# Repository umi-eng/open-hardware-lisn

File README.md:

# Open Hardware Dual DC LISN

This is a line impedance stabilization network for measuring conducted emissions to aid in evaluating designs for EMC compliance. It's based on an existing design from Rhode & Schwarz, which only existed as Gerber outputs.

This design is intended as a development tool and not suitable for empirical compliance testing.

## References

- [A homemade LISN for precompliance conducted emission tests on DC-DC power supplies - Rhode & Schwarz](https://www.rohde-schwarz.com/au/applications/a-homemade-lisn-for-precompliance-conducted-emission-tests-on-dc-dc-power-supplies_56279-1010752.html)

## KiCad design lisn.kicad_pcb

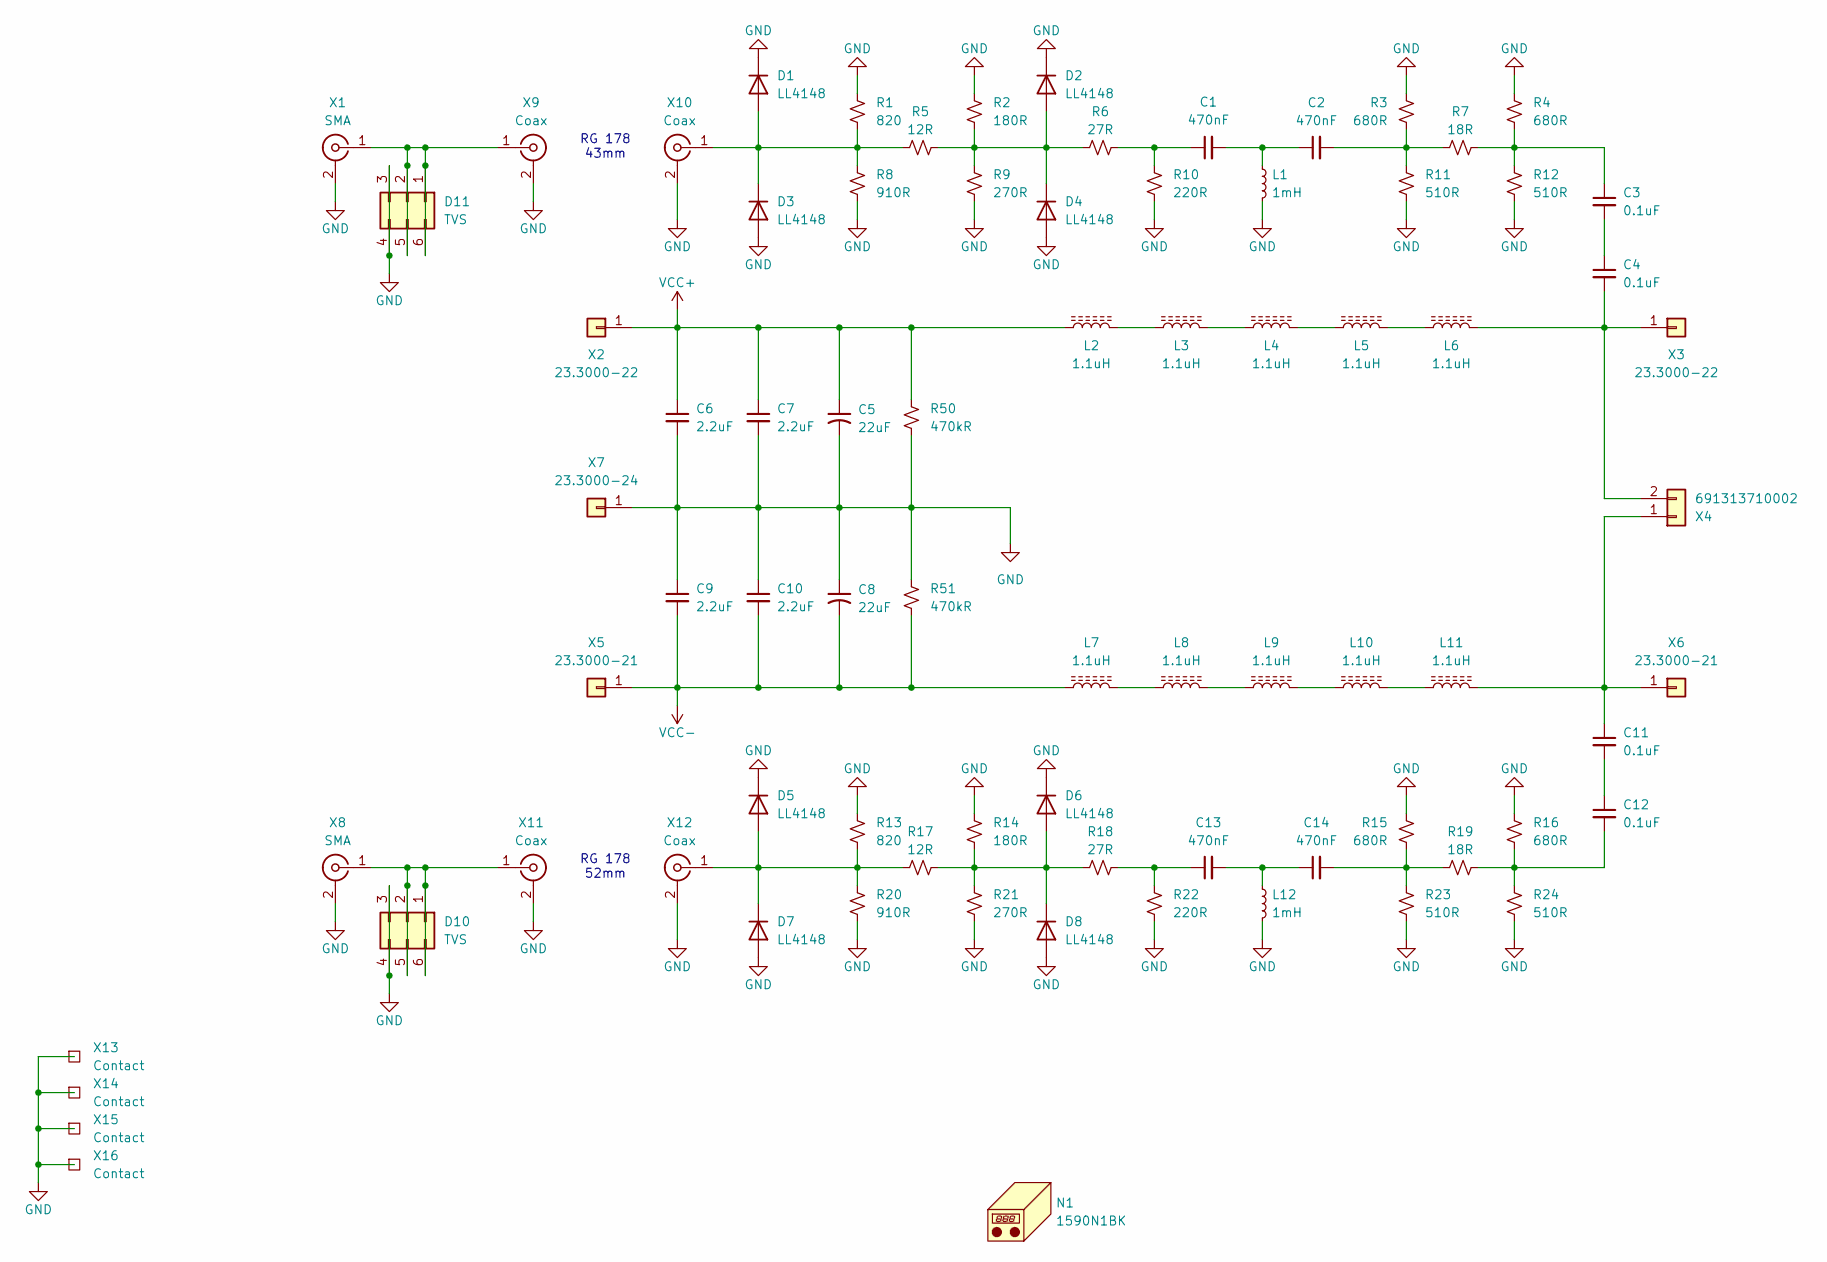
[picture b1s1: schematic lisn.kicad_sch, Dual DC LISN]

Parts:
C1, C2, C13, C14: 470nF; C_0805_2012Metric; Voltage 50V; Mouser 710-885012207102
C3, C4, C11, C12: 0.1uF; C_1206_3216Metric; Voltage 250V; Mouser 710-885342208004
C5, C8: 22uF; CP_Elec_8x10.5; Voltage 100V; Mouser 710-865060853003
C6, C7, C9, C10: 2.2uF; C_1210_3225Metric; Voltage 100V; Mouser 710-885012209071
D1, D2, D3, D4, D5, D6, D7, D8: LL4148; D_MiniMELF; Mouser 78-LL4148-M-08
D10, D11: TVS; DFN-6_1.3x1.2mm_P0.4mm; Mouser 710-824012823
L1, L12: 1mH; L_Wuerth_HCI-5040; Mouser 710-74404054102
L2, L3, L4, L5, L6, L7, L8, L9, L10, L11: 1.1uH; L_Wuerth_HCI-7050; Mouser 710-744314110
N1: 1590N1BK; Mouser 546-1590N1-BK
R1, R13: 820; R_0603_1608Metric; Mouser 667-ERJ-3EKF8200V
R2, R14: 180R; R_0603_1608Metric; Mouser 667-ERJ-3EKF1800V
R3, R4, R15, R16: 680R; R_0603_1608Metric; Mouser 667-ERJ-3EKF6800V
R5, R17: 12R; R_0603_1608Metric; Mouser 667-ERJ-3EKF12R0V
R6, R18: 27R; R_0603_1608Metric; Mouser 667-ERJ-3EKF27R0V
R7, R19: 18R; R_0603_1608Metric; Mouser 667-ERJ-3EKF18R0V
R8, R20: 910R; R_0603_1608Metric; Mouser 667-ERJ-3EKF9100V
R9, R21: 270R; R_0603_1608Metric; Mouser 667-ERJ-3EKF2700V
R10, R22: 220R; R_0603_1608Metric; Mouser 667-ERJ-3EKF2200V
R11, R12, R23, R24: 510R; R_0603_1608Metric; Mouser 667-ERJ-3EKF5100V
R50, R51: 470kR; R_0603_1608Metric; Mouser 667-ERJ-3EKF4703V
X1, X8: SMA; SMA_Amphenol_132289_EdgeMount; Mouser 710-60312242114510
X2, X3: 23.3000-22; STAUBLI_23.3000-22_Red
X4: 691313710002; PhoenixContact_MSTBA_2,5_2-G-5,08_1x02_P5.08mm_Horizontal; Mouser 710-691313710002
X5, X6: 23.3000-21; STAUBLI_23.3000-21_Black
X7: 23.3000-24; STAUBLI_23.3000-24_Yellow
X9, X10, X11, X12: Coax; Jumper_RG178
X13, X14, X15, X16: Contact; Wurth_331161702513; Mouser 710-331161702513

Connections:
GND: C5.2, C6.2, C7.2, C8.1, C9.1, C10.1, D1.1 (K), D2.1 (K), D3.2 (A), D4.2 (A), D5.1 (K), D6.1 (K), D7.2 (A), D8.2 (A), D10.3, D10.4, D11.3, D11.4, L1.2, L12.2, R1.1, R2.1, R3.1, R4.1, R8.2, R9.2, R10.2, R11.2, R12.2, R13.1, R14.1, R15.1, R16.1, R20.2, R21.2, R22.2, R23.2, R24.2, R50.2, R51.1, X1.2 (Ext), X7.1 (Pin_1_1), X8.2 (Ext), X9.2 (Ext), X10.2 (Ext), X11.2 (Ext), X12.2 (Ext), X13.1 (1_1), X14.1 (1_1), X15.1 (1_1), X16.1 (1_1)
unnamed: C1.1, R6.2, R10.1
unnamed: C1.2, C2.1, L1.1
unnamed: C2.2, R3.2, R7.1, R11.1
unnamed: C3.1, R4.2, R7.2, R12.1
unnamed: C3.2, C4.1
unnamed: C11.2, C12.1
unnamed: C12.2, R16.2, R19.2, R24.1
unnamed: C13.1, R18.2, R22.1
unnamed: C13.2, C14.1, L12.1
unnamed: C14.2, R15.2, R19.1, R23.1
unnamed: D1.2 (A), D3.1 (K), R1.2, R5.1, R8.1, X10.1 (In)
unnamed: D2.2 (A), D4.1 (K), R2.2, R5.2, R6.1, R9.1
unnamed: D5.2 (A), D7.1 (K), R13.2, R17.1, R20.1, X12.1 (In)
unnamed: D6.2 (A), D8.1 (K), R14.2, R17.2, R18.1, R21.1
unnamed: D10.1, D10.2, D10.5, D10.6, X8.1 (In), X11.1 (In)
unnamed: D11.1, D11.2, D11.5, D11.6, X1.1 (In), X9.1 (In)
unnamed: L2.2, L3.1
unnamed: L3.2, L4.1
unnamed: L4.2, L5.1
unnamed: L5.2, L6.1
unnamed: L7.2, L8.1
unnamed: L8.2, L9.1
unnamed: L9.2, L10.1
unnamed: L10.2, L11.1
unnamed: C4.2, L6.2, X3.1 (Pin_1_1), X4.2
unnamed: C11.1, L11.2, X4.1, X6.1 (Pin_1_1)
VCC+: C5.1, C6.1, C7.1, L2.1, R50.1, X2.1 (Pin_1_1)
VCC-: C8.2, C9.2, C10.2, L7.1, R51.2, X5.1 (Pin_1_1)

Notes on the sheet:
RG 178 52mm
RG 178 43mm

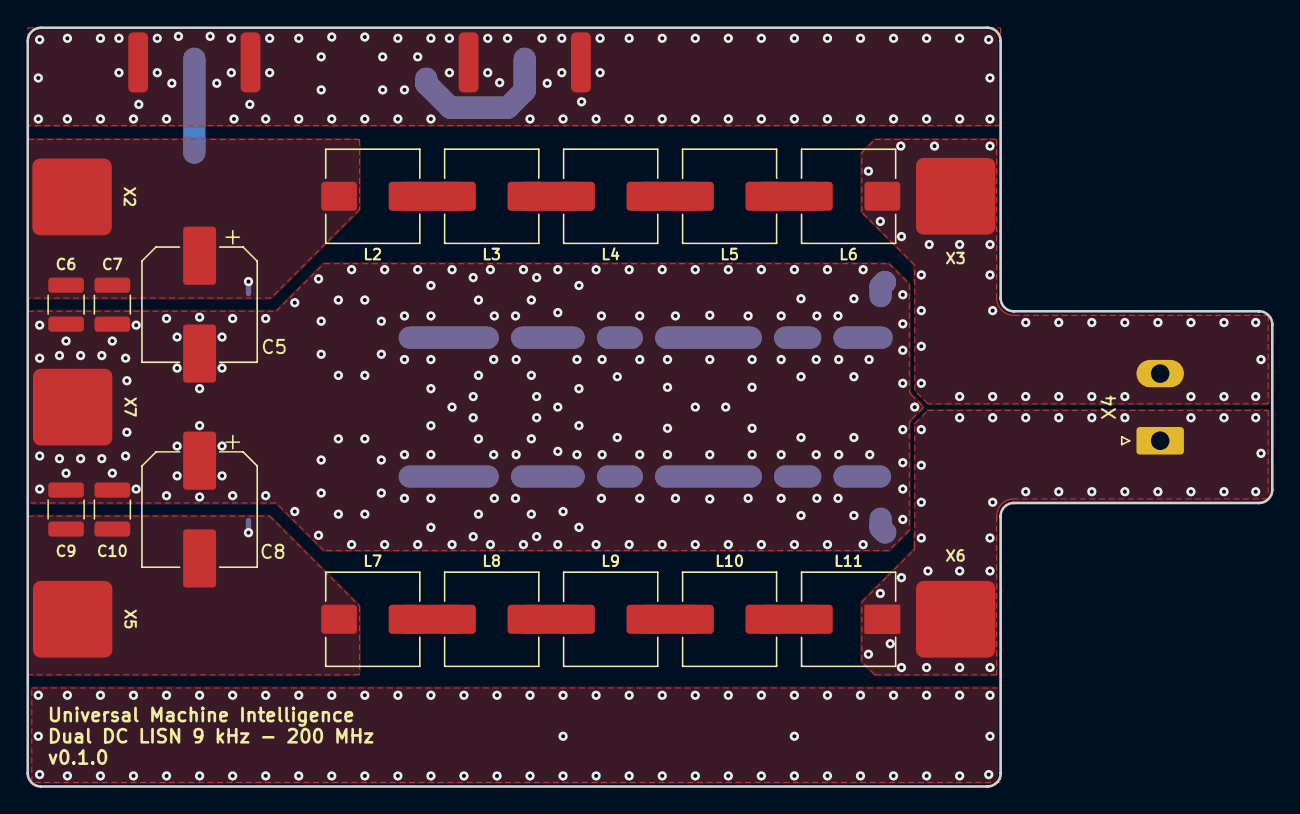
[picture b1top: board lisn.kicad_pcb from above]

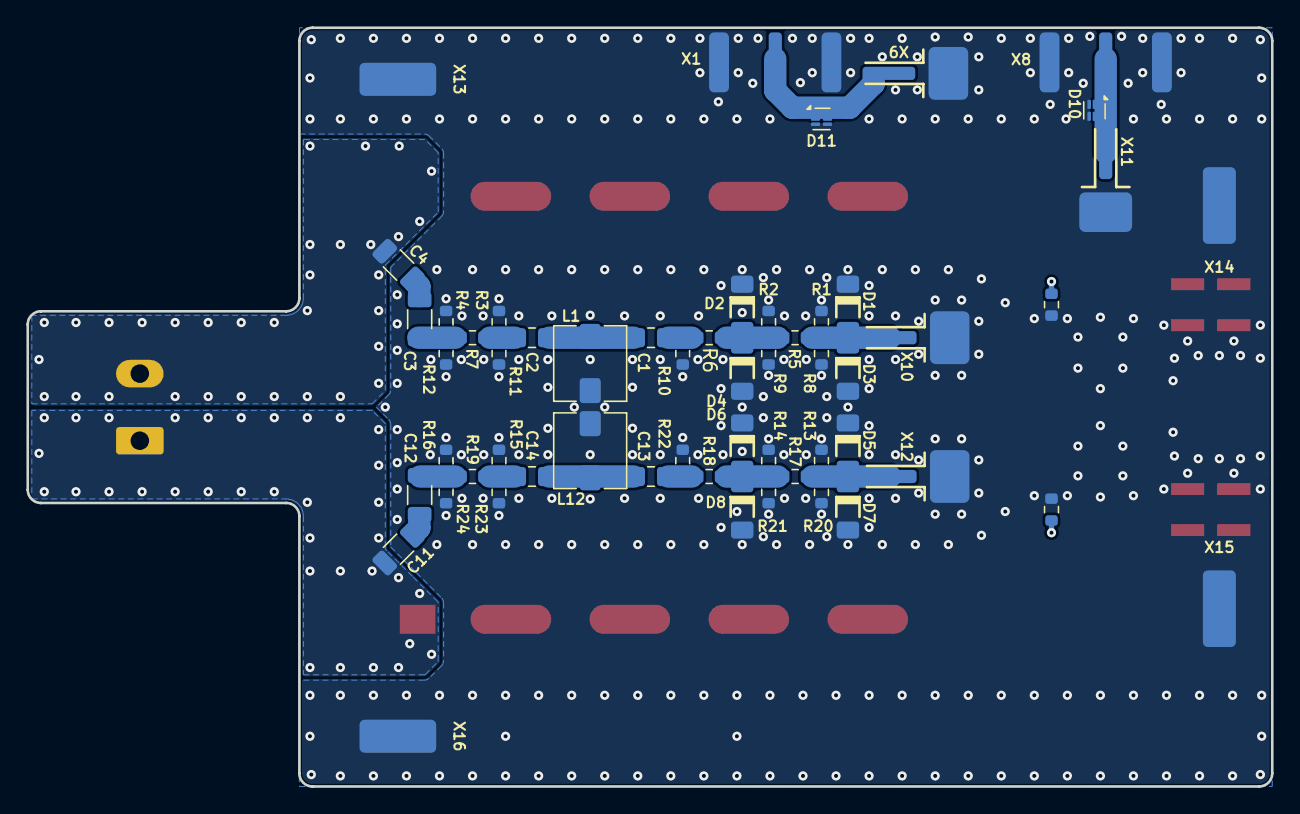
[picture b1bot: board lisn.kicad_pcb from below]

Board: 2 copper layers, 94.2 x 57.4 mm, 78 parts (56 on the bottom side), 29 nets.
